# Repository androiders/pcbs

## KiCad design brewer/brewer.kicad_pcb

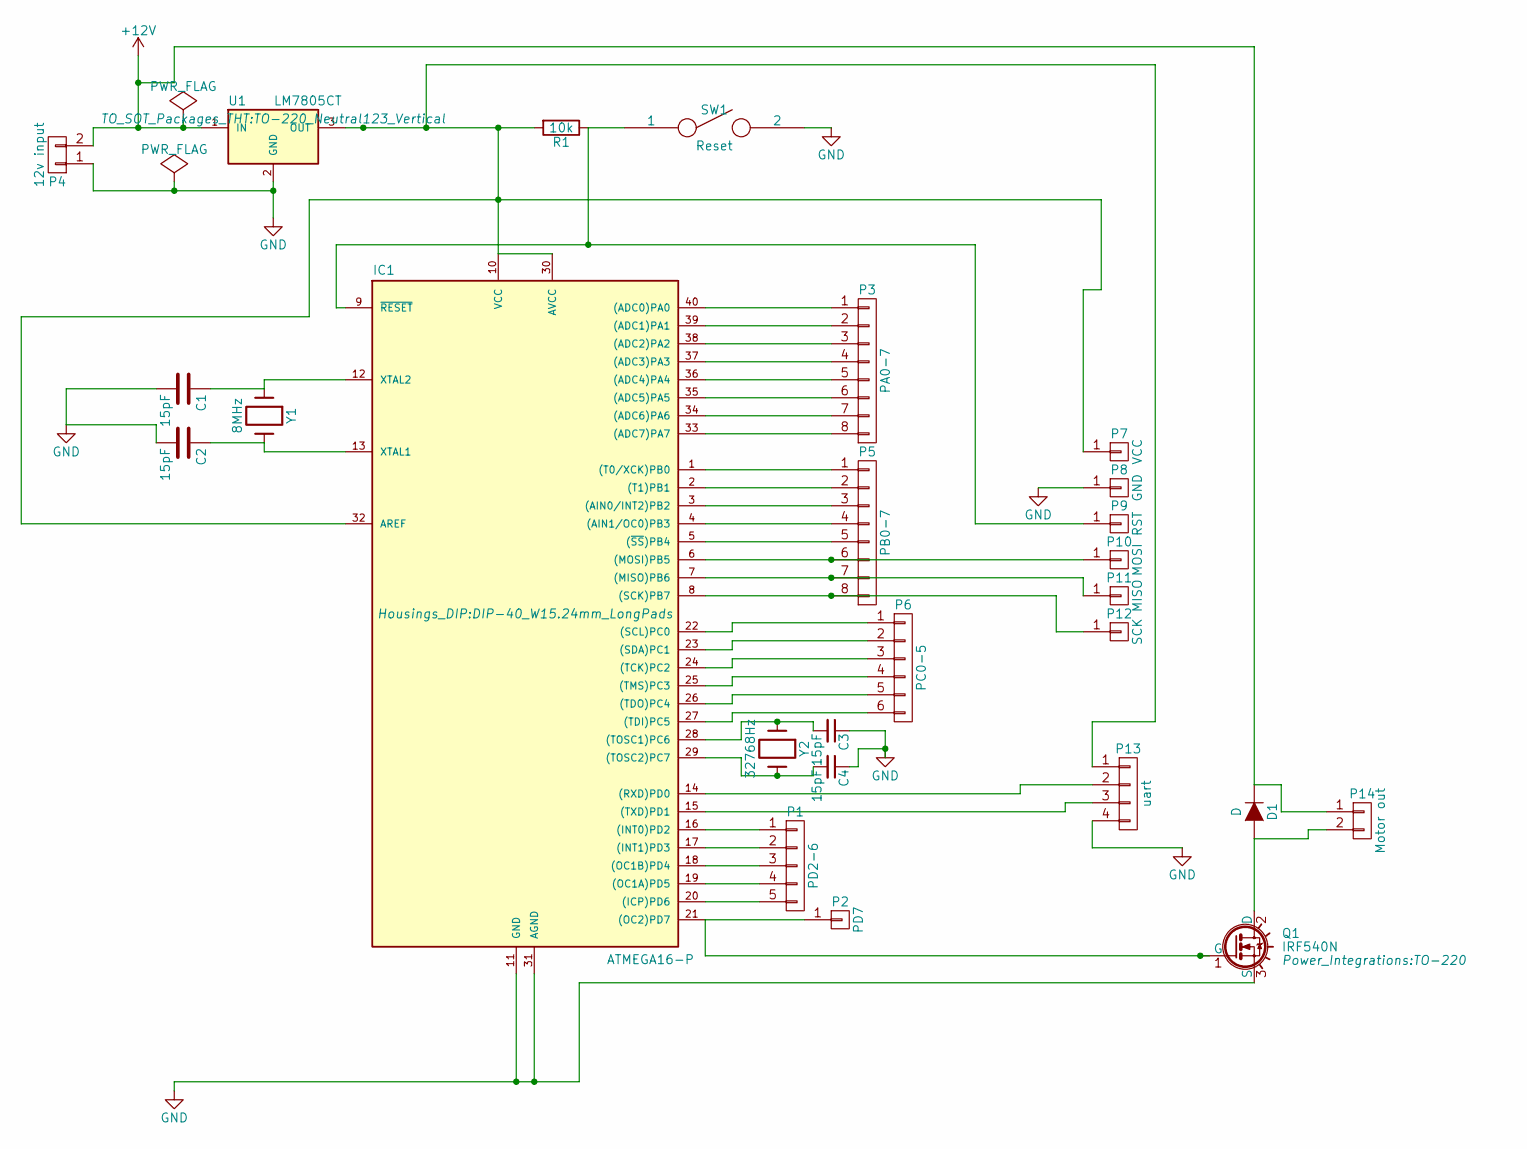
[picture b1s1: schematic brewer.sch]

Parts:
C1, C2, C3, C4: 15pF; C_Disc_D3_P2.5
D1: D; Resistor_Horizontal_RM7mm
IC1: ATMEGA16-P; DIP-40_W15.24mm_LongPads
P1: PD2-6; Pin_Header_Straight_1x05
P2: PD7; Pin_Header_Straight_1x01
P3: PA0-7; Pin_Header_Straight_1x08
P4: 12v input; TerminalBlock_Pheonix_MPT-2.54mm_2pol
P5: PB0-7; Pin_Header_Straight_1x08
P6: PC0-5; Pin_Header_Straight_1x06
P7: VCC; Pin_Header_Straight_1x01
P8: GND; Pin_Header_Straight_1x01
P9: RST; Pin_Header_Straight_1x01
P10: MOSI; Pin_Header_Straight_1x01
P11: MISO; Pin_Header_Straight_1x01
P12: SCK; Pin_Header_Straight_1x01
P13: uart; Pin_Header_Straight_1x04
P14: Motor out; TerminalBlock_Pheonix_MPT-2.54mm_2pol
Q1: IRF540N; TO-220
R1: 10k; Resistor_Horizontal_RM7mm
SW1: Reset; SW_SPST_EVQPE1
U1: LM7805CT; TO-220_Neutral123_Vertical
Y1: 8MHz; Crystal_HC49-U_Vertical
Y2: 32768Hz; Crystal_Round_Horizontal_2mm

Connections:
+12V: D1.1 (K), P4.2, P14.1, U1.1 (IN)
GND: C1.2, C2.2, C3.1, C4.1, IC1.11 (GND), IC1.31 (AGND), P4.1, P8.1, P13.4, Q1.3 (S), SW1.2, U1.2 (GND)
unnamed: C1.1, IC1.12 (XTAL2), Y1.1
unnamed: C2.1, IC1.13 (XTAL1), Y1.2
unnamed: C3.2, IC1.28 ((TOSC1)PC6), Y2.1
unnamed: C4.2, IC1.29 ((TOSC2)PC7), Y2.2
unnamed: D1.2 (A), P14.2, Q1.2 (D)
unnamed: IC1.1 ((T0/XCK)PB0), P5.1
unnamed: IC1.2 ((T1)PB1), P5.2
unnamed: IC1.3 ((AIN0/INT2)PB2), P5.3
unnamed: IC1.4 ((AIN1/OC0)PB3), P5.4
unnamed: IC1.5 ((~SS~)PB4), P5.5
unnamed: IC1.6 ((MOSI)PB5), P5.6, P10.1
unnamed: IC1.7 ((MISO)PB6), P5.7, P11.1
unnamed: IC1.8 ((SCK)PB7), P5.8, P12.1
unnamed: IC1.9 (~RESET), P9.1, R1.1, SW1.1
unnamed: IC1.10 (VCC), IC1.30 (AVCC), IC1.32 (AREF), P7.1, P13.1, R1.2, U1.3 (OUT)
unnamed: IC1.14 ((RXD)PD0), P13.2
unnamed: IC1.15 ((TXD)PD1), P13.3
unnamed: IC1.16 ((INT0)PD2), P1.1
unnamed: IC1.17 ((INT1)PD3), P1.2
unnamed: IC1.18 ((OC1B)PD4), P1.3
unnamed: IC1.19 ((OC1A)PD5), P1.4
unnamed: IC1.20 ((ICP)PD6), P1.5
unnamed: IC1.21 ((OC2)PD7), P2.1, Q1.1 (G)
unnamed: IC1.22 ((SCL)PC0), P6.1
unnamed: IC1.23 ((SDA)PC1), P6.2
unnamed: IC1.24 ((TCK)PC2), P6.3
unnamed: IC1.25 ((TMS)PC3), P6.4
unnamed: IC1.26 ((TDO)PC4), P6.5
unnamed: IC1.27 ((TDI)PC5), P6.6
unnamed: IC1.33 ((ADC7)PA7), P3.8
unnamed: IC1.34 ((ADC6)PA6), P3.7
unnamed: IC1.35 ((ADC5)PA5), P3.6
unnamed: IC1.36 ((ADC4)PA4), P3.5
unnamed: IC1.37 ((ADC3)PA3), P3.4
unnamed: IC1.38 ((ADC2)PA2), P3.3
unnamed: IC1.39 ((ADC1)PA1), P3.2
unnamed: IC1.40 ((ADC0)PA0), P3.1

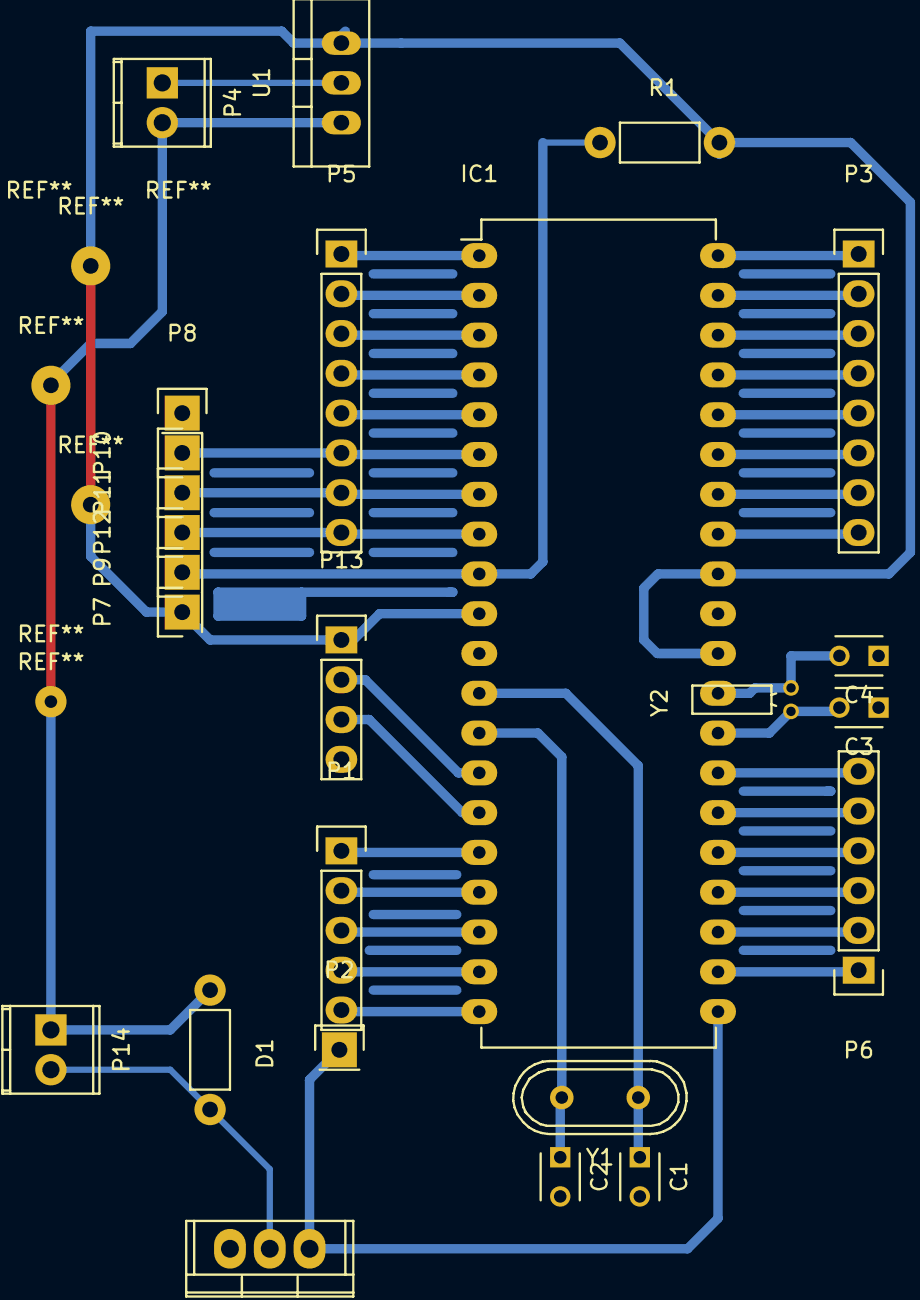
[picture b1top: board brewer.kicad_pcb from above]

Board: 2 copper layers, 26 parts (1 on the bottom side), 39 nets.

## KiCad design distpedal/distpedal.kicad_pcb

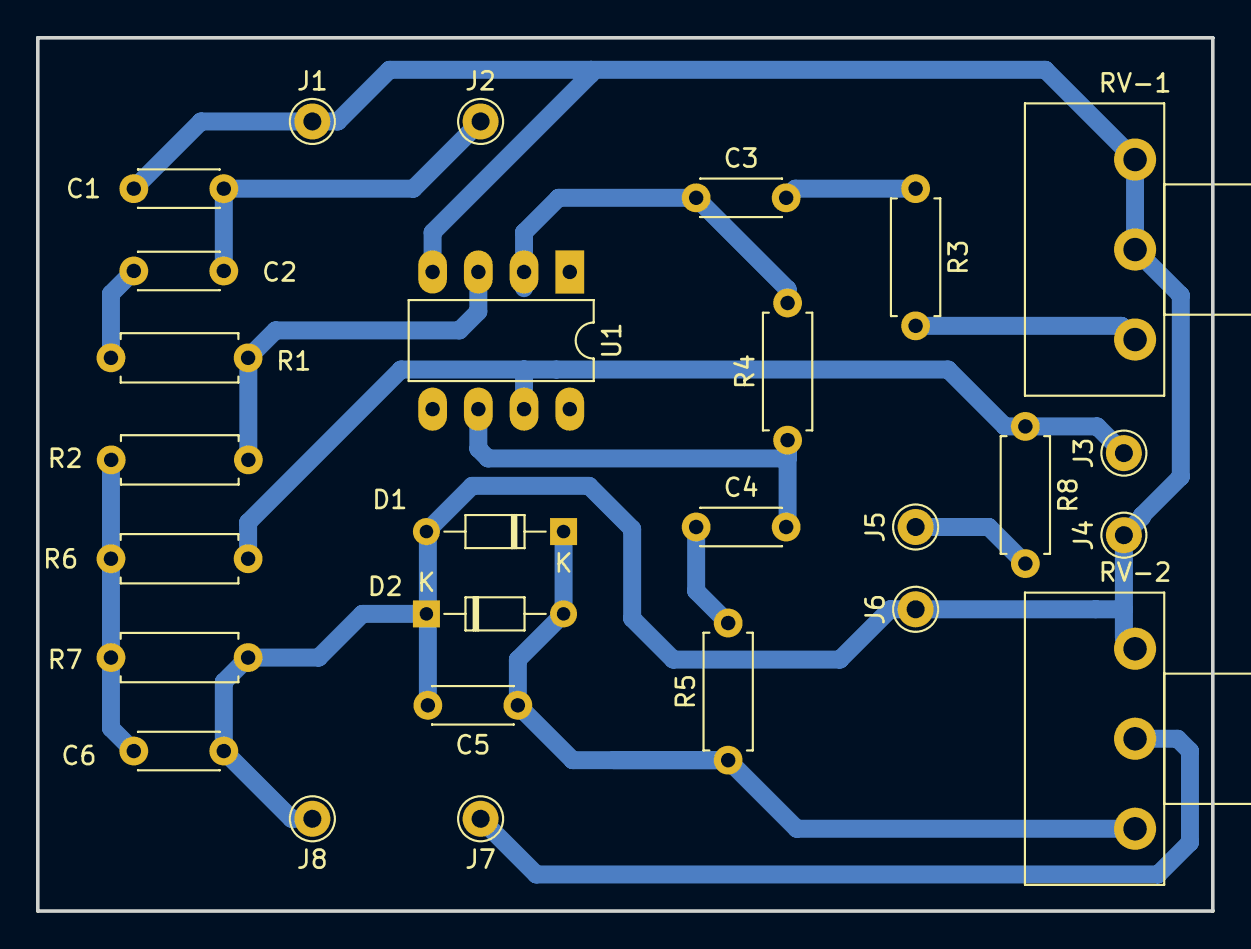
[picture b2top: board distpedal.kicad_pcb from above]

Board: 2 copper layers, 65.3 x 48.5 mm, 27 parts (0 on the bottom side), 14 nets.

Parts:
C1, C5: 1nF; C_Disc_D4.3mm_W1.9mm_P5.00mm
C2: 10n; C_Disc_D4.3mm_W1.9mm_P5.00mm
C3: 47nF; C_Disc_D4.3mm_W1.9mm_P5.00mm
C4, C6: 1uF; C_Disc_D4.3mm_W1.9mm_P5.00mm
D1, D2: D; D_DO-34_SOD68_P7.62mm_Horizontal
J1: Insleeve; Pin_D1.0mm_L10.0mm
J2: Intip; Pin_D1.0mm_L10.0mm
J3: 9vin; Pin_D1.0mm_L10.0mm
J4: gnd in; Pin_D1.0mm_L10.0mm
J5: Led+; Pin_D1.0mm_L10.0mm
J6: Led-; Pin_D1.0mm_L10.0mm
J7: Outtip; Pin_D1.0mm_L10.0mm
J8: Outsleve; Pin_D1.0mm_L10.0mm
R1, R5: 10K; R_Axial_DIN0207_L6.3mm_D2.5mm_P7.62mm_Horizontal
R2, R4, R6, R7: 1M; R_Axial_DIN0207_L6.3mm_D2.5mm_P7.62mm_Horizontal
R3: 4K7; R_Axial_DIN0207_L6.3mm_D2.5mm_P7.62mm_Horizontal
R8: R; R_Axial_DIN0207_L6.3mm_D2.5mm_P7.62mm_Horizontal
RV-1: 1M; Potentiometer_Piher_T-16H_Single_Horizontal
RV-2: 10K; Potentiometer_Piher_T-16H_Single_Horizontal
U1: lm741; DIP-8_W7.62mm_LongPads

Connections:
+9V: J3.1, R6.1, R8.1, U1.7
/4.5V: C6.1, R2.1, R6.2, R7.1
GNDREF: C1.1, C5.2, C6.2, D1.2, D2.1, J1.1, J4.1, J6.1, J8.1, R7.2, RV-1.2, RV-1.3, RV-2.3, U1.4
unnamed: C1.2, C2.2, J2.1
unnamed: C2.1, R1.2
unnamed: C3.1, R4.2, U1.2
unnamed: C3.2, R3.1
unnamed: C4.1, R5.2
unnamed: C4.2, R4.1, U1.6
unnamed: C5.1, D1.1, D2.2, R5.1, RV-2.1
unnamed: J5.1, R8.2
unnamed: J7.1, RV-2.2
unnamed: R1.1, R2.2, U1.3
unnamed: R3.2, RV-1.1

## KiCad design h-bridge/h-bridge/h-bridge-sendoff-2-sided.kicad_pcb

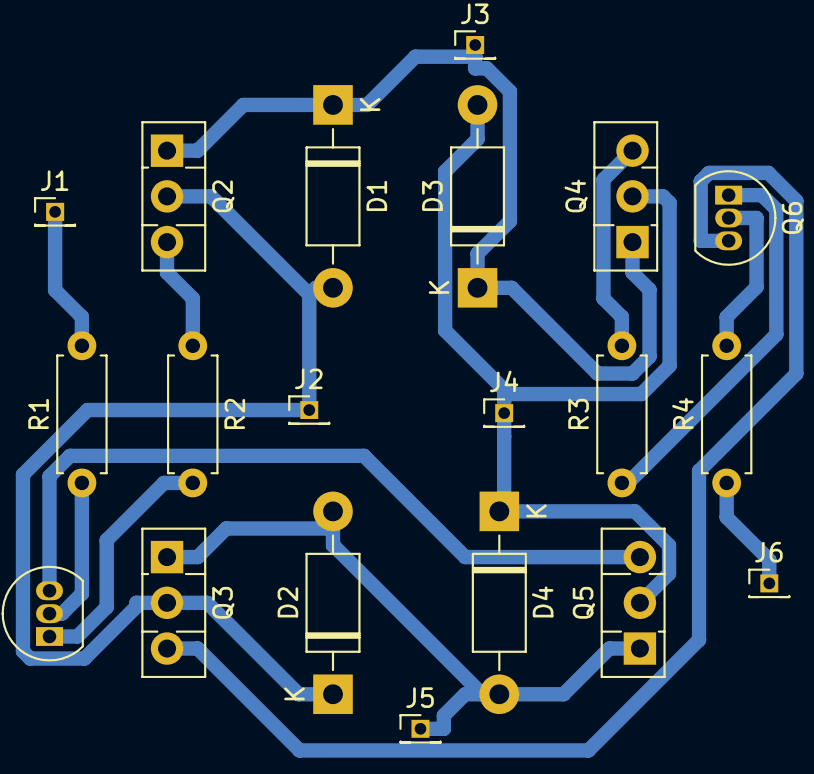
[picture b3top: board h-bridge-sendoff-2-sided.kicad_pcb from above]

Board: 2 copper layers, 20 parts (0 on the bottom side), 14 nets.

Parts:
D1, D2, D3, D4: 1N4001; D_DO-41_SOD81_P10.16mm_Horizontal
J1, J2, J3, J4, J5, J6: Conn_01x01_Male; PinHeader_1x01_P1.27mm_Vertical
Q1, Q6: BC547; TO-92_Inline
Q2, Q4: BD140; TO-126-3_Vertical
Q3, Q5: BD139; TO-126-3_Vertical
R1, R2, R3, R4: R; R_Axial_DIN0207_L6.3mm_D2.5mm_P7.62mm_Horizontal

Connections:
GND: D2.2, D4.2, J5.1, Q3.1, Q5.1
unnamed: D1.1, D3.1, J3.1, Q2.1, Q4.1
unnamed: D1.2, D2.1, J2.1, Q2.2, Q3.2
unnamed: D3.2, D4.1, J4.1, Q4.2, Q5.2
unnamed: J1.1, R1.2
unnamed: J6.1, R4.1
unnamed: Q1.1, R2.2
unnamed: Q1.2, R1.1
unnamed: Q1.3, Q5.3
unnamed: Q2.3, R2.1
unnamed: Q3.3, Q6.3
unnamed: Q4.3, R3.2
unnamed: Q6.1, R3.1
unnamed: Q6.2, R4.2

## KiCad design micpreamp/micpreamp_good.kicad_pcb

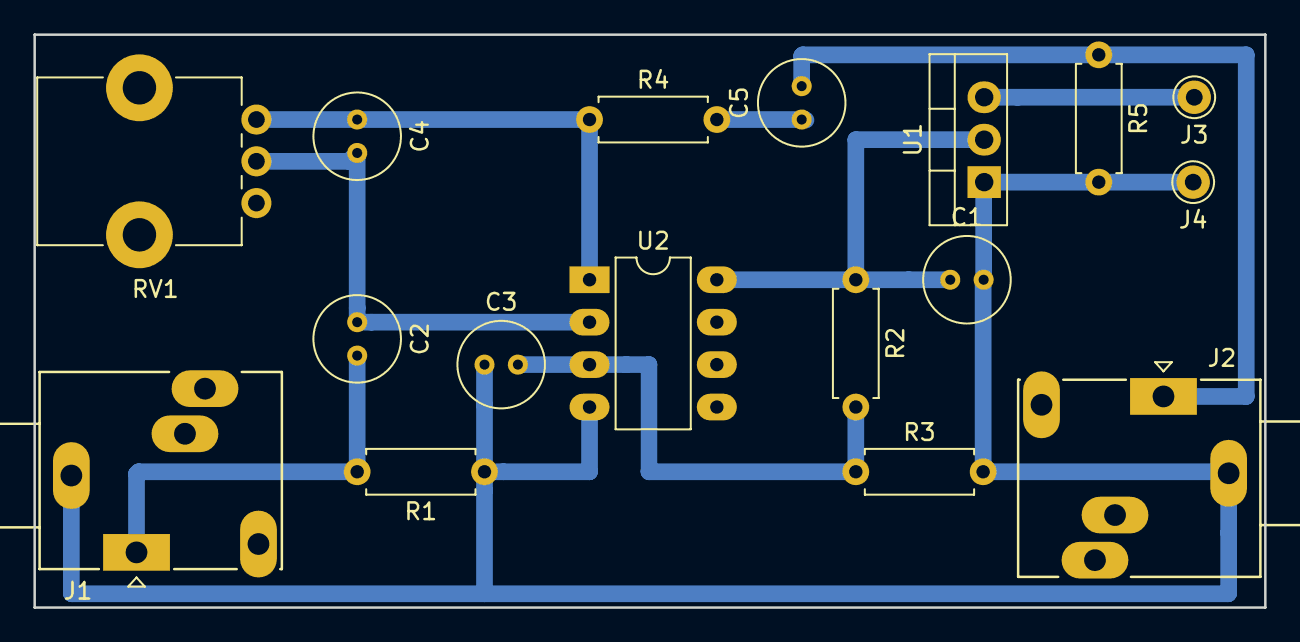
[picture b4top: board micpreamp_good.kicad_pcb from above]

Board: 2 copper layers, 73.7 x 34.3 mm, 17 parts (0 on the bottom side), 9 nets.

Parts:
C1, C4: 15pF; C_Radial_D5.0mm_H5.0mm_P2.00mm
C2, C5: 2.2uF; C_Radial_D5.0mm_H5.0mm_P2.00mm
C3: 20pF; C_Radial_D5.0mm_H5.0mm_P2.00mm
J1: Input; StereoJack_3.5mm_Switch_Ledino_KB3SPRS_Horizontal
J2: Output; StereoJack_3.5mm_Switch_Ledino_KB3SPRS_Horizontal
J3: Vdd; Pin_D1.0mm_L10.0mm
J4: Gnd; Pin_D1.0mm_L10.0mm
R1: 2K7; R_Axial_DIN0207_L6.3mm_D2.5mm_P7.62mm_Horizontal
R2, R3: 56K; R_Axial_DIN0207_L6.3mm_D2.5mm_P7.62mm_Horizontal
R4: 47; R_Axial_DIN0207_L6.3mm_D2.5mm_P7.62mm_Horizontal
R5: 10K; R_Axial_DIN0207_L6.3mm_D2.5mm_P7.62mm_Horizontal
RV1: 100K; Potentiometer_Alps_RK09K_Single_Vertical
U1: 3.3 reg; TO-220-3_Vertical
U2: LM358; DIP-8_W7.62mm_LongPads

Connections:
GND: C1.2, C3.1, J1.S, J2.S, J4.1, R1.1, R3.2, R5.2, U1.1, U2.4
unnamed: C1.1, R2.1, U1.2, U2.8
unnamed: C2.1, C4.2, RV1.2, U2.2
unnamed: C2.2, J1.T, R1.2
unnamed: C3.2, R2.2, R3.1, U2.3
unnamed: C4.1, R4.1, RV1.1, U2.1
unnamed: C5.1, R4.2
unnamed: C5.2, J2.T, R5.1
unnamed: J3.1, U1.3

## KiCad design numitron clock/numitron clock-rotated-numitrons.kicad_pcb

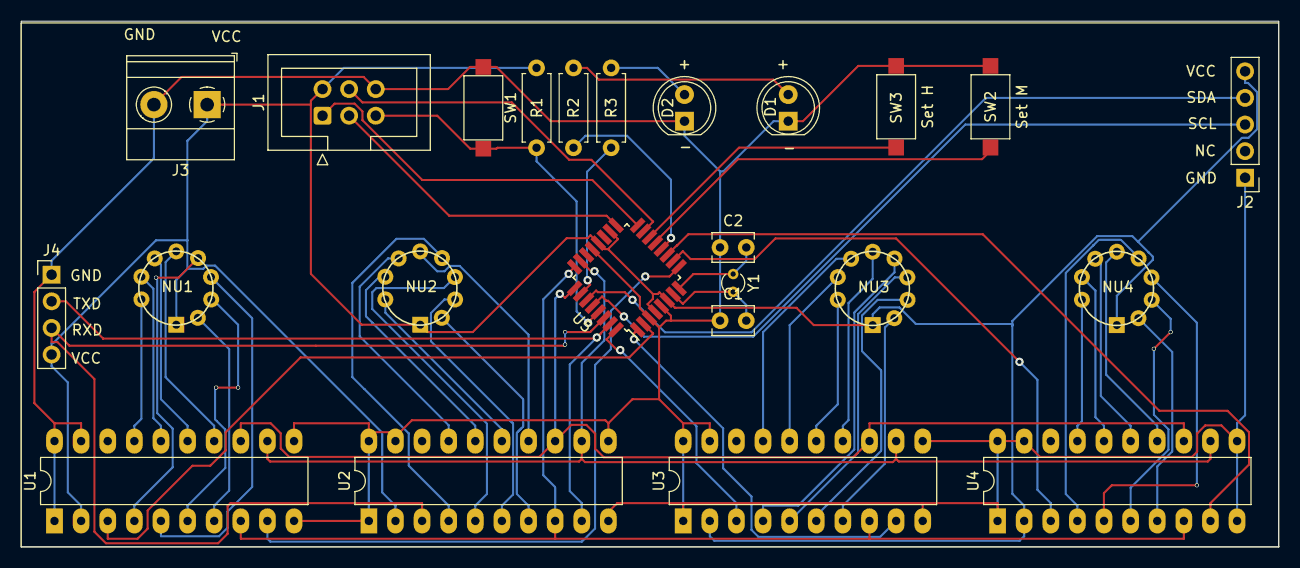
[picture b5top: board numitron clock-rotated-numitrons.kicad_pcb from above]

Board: 2 copper layers, 120.0 x 50.2 mm, 24 parts (0 on the bottom side), 59 nets.

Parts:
C1, C2: C; C_Disc_D3.8mm_W2.6mm_P2.50mm
D1, D2: LED; LED_D5.0mm
J1: AVR-ISP-6; IDC-Header_2x03_P2.54mm_Vertical
J2: rtc; PinHeader_1x05_P2.54mm_Vertical
J3: 5v in; TerminalBlock_Phoenix_MKDS-1,5-2-5.08_1x02_P5.08mm_Horizont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
J4: UART; PinHeader_1x04_P2.54mm_Vertical
NU1, NU2, NU3, NU4: Numitron_IV-9; numitron iv-9
R1, R2, R3: R; R_Axial_DIN0207_L6.3mm_D2.5mm_P7.62mm_Horizontal
SW1: RST; SW_SPST_CK_RS282G05A3
SW2: Set M; SW_SPST_CK_RS282G05A3
SW3: Set H; SW_SPST_CK_RS282G05A3
U1, U2, U3, U4: TPIC6595; DIP-20_W7.62mm_LongPads
U5: ATmega8L-8A; TQFP-32_7x7mm_P0.8mm
Y1: Crystal; Crystal_Round_D1.5mm_Vertical

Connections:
D1: R2.1, U5.12 (PB0)
D2: R3.1, U5.26 (PC3)
G1: J4.2, U2.9 (~G), U5.31 (PD1)
G2: U3.9 (~G), U5.1 (PD3)
G3: U1.9 (~G), U5.9 (PD5)
G4: U4.9 (~G), U5.11 (PD7)
GNDREF: C1.1, C2.1, D1.1 (K), D2.1 (K), J1.6 (GND), J2.1, J3.2, J4.1, SW1.1, SW2.2, SW3.2, U1.1 (PGND), U1.10 (PGND), U1.11 (PGND), U1.19 (LGND), U1.20 (PGND), U2.1 (PGND), U2.10 (PGND), U2.11 (PGND), U2.19 (LGND), U2.20 (PGND), U3.1 (PGND), U3.10 (PGND), U3.11 (PGND), U3.19 (LGND), U3.20 (PGND), U4.1 (PGND), U4.10 (PGND), U4.11 (PGND), U4.19 (LGND), U4.20 (PGND), U5.3 (GND), U5.5 (GND), U5.21 (AGND)
MISO: J1.1 (MISO), U5.16 (PB4)
MOSI: J1.4 (MOSI), U5.15 (PB3)
unnamed: C1.2, U5.7 (PB6/XTAL1), Y1.2
unnamed: C2.2, U5.8 (PB7/XTAL2), Y1.1
unnamed: D1.2 (A), R2.2
unnamed: D2.2 (A), R3.2
unnamed: J2.3, U5.28 (PC5)
unnamed: J2.4, U5.27 (PC4)
unnamed: NU1.2 (DP), U1.7 (DRAIN3)
unnamed: NU1.3 (B), U1.6 (DRAIN2)
unnamed: NU1.4 (C), U1.5 (DRAIN1)
unnamed: NU1.5 (A), U1.4 (DRAIN0)
unnamed: NU1.6 (F), U1.14 (DRAIN4)
unnamed: NU1.7 (G), U1.15 (DRAIN5)
unnamed: NU1.8 (D), U1.16 (DRAIN6)
unnamed: NU1.9 (E), U1.17 (DRAIN7)
unnamed: NU3.2 (DP), U3.7 (DRAIN3)
unnamed: NU3.3 (B), U3.6 (DRAIN2)
unnamed: NU3.4 (C), U3.5 (DRAIN1)
unnamed: NU3.5 (A), U3.4 (DRAIN0)
unnamed: NU3.6 (F), U3.14 (DRAIN4)
unnamed: NU3.7 (G), U3.17 (DRAIN7)
unnamed: NU3.8 (D), U3.16 (DRAIN6)
unnamed: NU3.9 (E), U3.15 (DRAIN5)
unnamed: SW2.1, U5.13 (PB1)
unnamed: SW3.1, U5.14 (PB2)
unnamed: NU2.5 (A), U2.4 (DRAIN0)
unnamed: NU2.4 (C), U2.5 (DRAIN1)
unnamed: NU2.3 (B), U2.6 (DRAIN2)
unnamed: NU2.2 (DP), U2.7 (DRAIN3)
unnamed: NU2.6 (F), U2.14 (DRAIN4)
unnamed: NU2.9 (E), U2.15 (DRAIN5)
unnamed: NU2.8 (D), U2.16 (DRAIN6)
unnamed: NU2.7 (G), U2.17 (DRAIN7)
unnamed: NU4.5 (A), U4.4 (DRAIN0)
unnamed: NU4.4 (C), U4.5 (DRAIN1)
unnamed: NU4.3 (B), U4.6 (DRAIN2)
unnamed: NU4.2 (DP), U4.7 (DRAIN3)
unnamed: NU4.6 (F), U4.14 (DRAIN4)
unnamed: NU4.7 (G), U4.15 (DRAIN5)
unnamed: NU4.8 (D), U4.16 (DRAIN6)
unnamed: NU4.9 (E), U4.17 (DRAIN7)
RCLK: U1.12 (RCLK), U2.12 (RCLK), U3.12 (RCLK), U4.12 (RCLK), U5.23 (PC0)
RST: J1.5 (~RST), R1.2, SW1.2, U5.29 (PC6/~RESET)
SCK: J1.3 (SCK), U5.17 (PB5)
SD1: J4.3, U2.3 (SER_IN), U5.30 (PD0)
SD2: U3.3 (SER_IN), U5.32 (PD2)
SD3: U1.3 (SER_IN), U5.2 (PD4)
SD4: U4.3 (SER_IN), U5.10 (PD6)
SRCK: U1.13 (SRCK), U2.13 (SRCK), U3.13 (SRCK), U4.13 (SRCK), U5.25 (PC2)
SRCLR: U1.8 (~SRCLR), U2.8 (~SRCLR), U3.8 (~SRCLR), U4.8 (~SRCLR), U5.24 (PC1)
VCC: J1.2 (VCC), J2.5, J3.1, J4.4, NU1.1 (Common), NU2.1 (Common), NU3.1 (Common), NU4.1 (Common), R1.1, U1.2 (VCC), U2.2 (VCC), U3.2 (VCC), U4.2 (VCC), U5.4 (VCC), U5.6 (VCC), U5.18 (AVCC), U5.20 (AREF)

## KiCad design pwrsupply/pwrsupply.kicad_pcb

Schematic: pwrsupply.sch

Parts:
C1, C2: 10uF; CP_Radial_D5.0mm_P2.50mm
J1: Conn_01x02; PinHeader_1x02_P2.54mm_Vertical
J2: Conn_01x04; PinHeader_1x04_P2.54mm_Vertical
R1, R2: 47K; R_Axial_DIN0207_L6.3mm_D2.5mm_P7.62mm_Horizontal
U1: LM2904; DIP-8_W7.62mm
U2: L7809; TO-220-3_Vertical
U3: LM7909_TO220; TO-220-3_Vertical

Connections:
unnamed: C1.1, J1.2, R1.1, U1.8, U2.1 (IN)
unnamed: C1.2, C2.1, J2.2, J2.3, U1.1, U1.2, U2.2 (GND), U3.1 (GND)
unnamed: C2.2, J1.1, R2.2, U1.4, U3.2 (VI)
unnamed: J2.1, U2.3 (OUT)
unnamed: J2.4, U3.3 (VO)
unnamed: R1.2, R2.1, U1.3

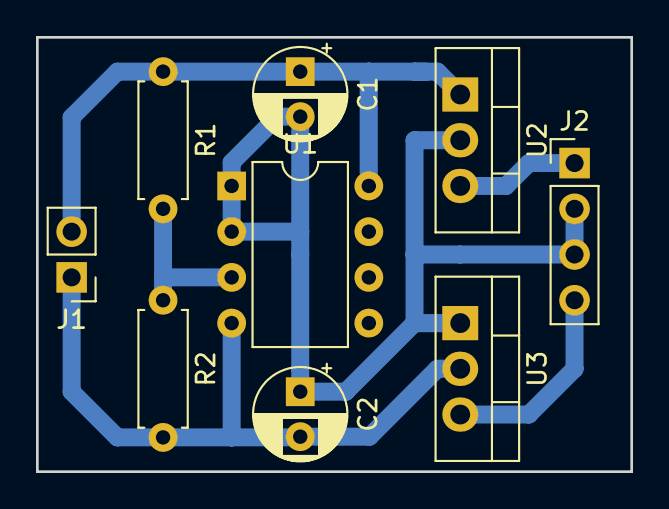
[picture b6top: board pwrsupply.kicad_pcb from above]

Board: 2 copper layers, 33.0 x 24.1 mm, 9 parts (0 on the bottom side), 6 nets.

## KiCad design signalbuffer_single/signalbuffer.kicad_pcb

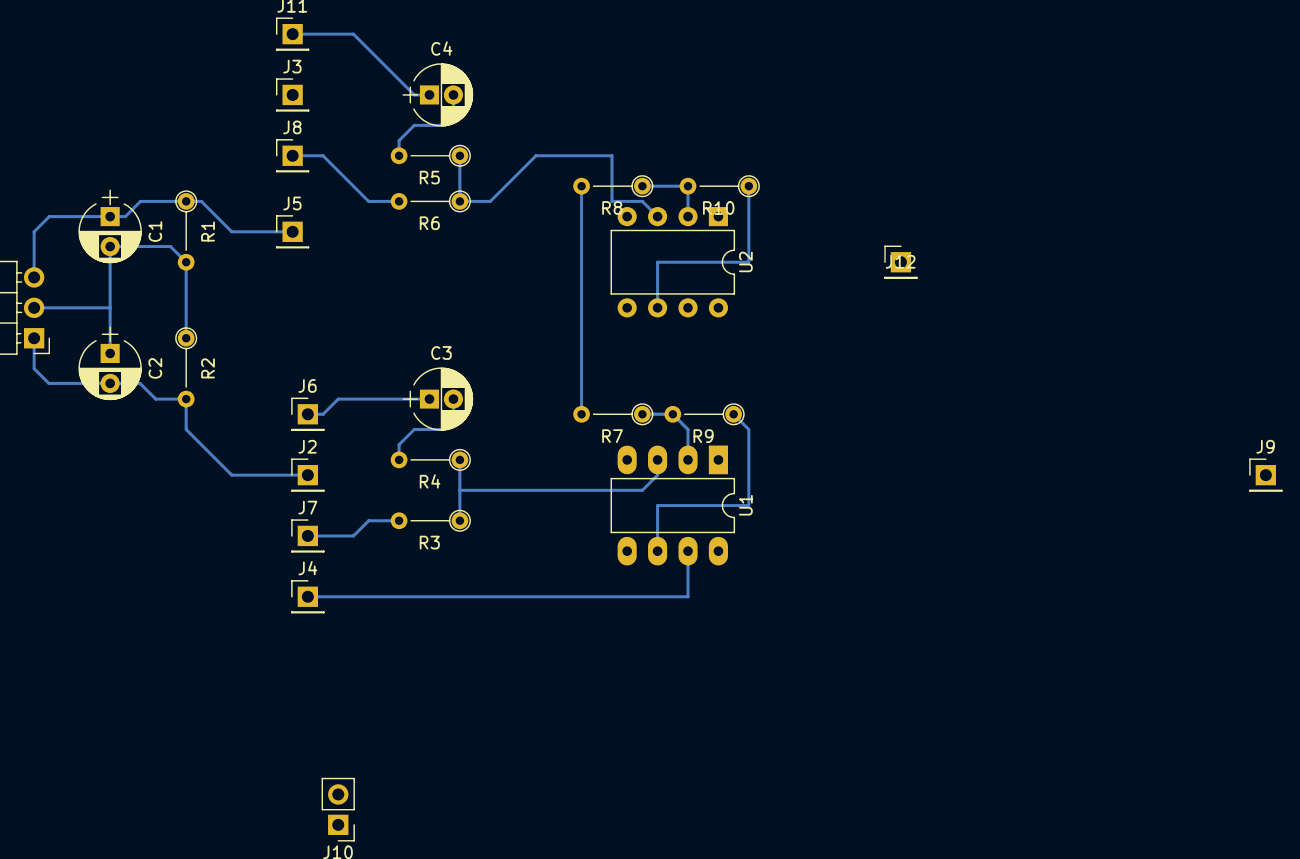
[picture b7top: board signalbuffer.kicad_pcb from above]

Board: 2 copper layers, 28 parts (0 on the bottom side), 15 nets.

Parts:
C1, C2: CP; CP_Radial_D5.0mm_P2.50mm
C3, C4: 47uF; CP_Radial_D5.0mm_P2.00mm
J1: 15v input; Pin_Header_Angled_1x03_Pitch2.54mm
J2: Bias1 neg; Pin_Header_Straight_1x01_Pitch2.54mm
J3: Bias2 neg; Pin_Header_Straight_1x01_Pitch2.54mm
J4: Bias1 Pos; Pin_Header_Straight_1x01_Pitch2.54mm
J5: Bias2 Pos; Pin_Header_Straight_1x01_Pitch2.54mm
J6: Signal SQR In; Pin_Header_Straight_1x01_Pitch2.54mm
J7: Bias1 In; Pin_Header_Straight_1x01_Pitch2.54mm
J8: Bias2 In; Pin_Header_Straight_1x01_Pitch2.54mm
J9: SQR out; Pin_Header_Straight_1x01_Pitch2.54mm
J10: Signals Gnd; Pin_Header_Straight_1x02_Pitch2.54mm
J11: Signal SIN In; Pin_Header_Straight_1x01_Pitch2.54mm
J12: SIN/TRI out; Pin_Header_Straight_1x01_Pitch2.54mm
R1, R2, R3, R4, R5, R6, R7, R8, R9, R10: R; R_Axial_DIN0204_L3.6mm_D1.6mm_P5.08mm_Vertical
U1: LM318N; DIP-8_W7.62mm_LongPads
U2: LM318N; DIP-8_W7.62mm

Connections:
GNDREF: C1.2, C2.1, J1.2, J10.1, J10.2, R1.2, R2.1, R7.2, R8.2
unnamed: C3.1, J6.1
unnamed: C3.2, R4.2
unnamed: C4.1, J11.1
unnamed: C4.2, R5.2
unnamed: J7.1, R3.2
unnamed: J8.1, R6.2
unnamed: J9.1, R9.1, U1.6
unnamed: J12.1, R10.1, U2.6
unnamed: R3.1, R4.1, U1.3
unnamed: R5.1, R6.1, U2.3
unnamed: R7.1, R9.2, U1.2
unnamed: R8.1, R10.2, U2.2
VDD: C1.1, J1.3, J4.1, J5.1, R1.1, U1.7, U2.7
VSS: C2.2, J1.1, J2.1, J3.1, R2.2, U1.4, U2.4
